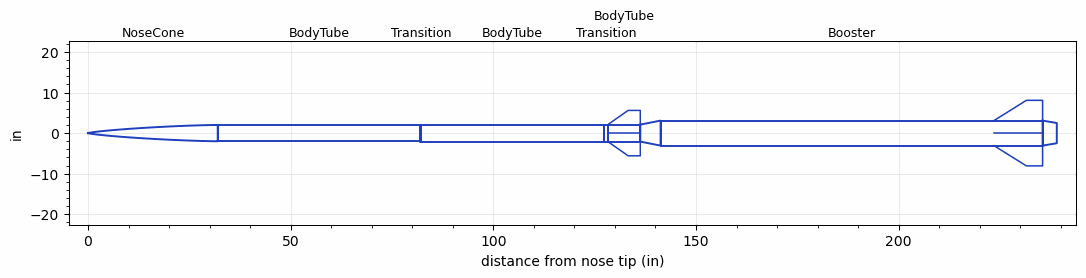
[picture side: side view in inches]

<RASAeroDocument>
 <FileVersion>2</FileVersion>
 <RocketDesign>
  <NoseCone>
   <Length>32</Length>
   <Diameter>4.02</Diameter>
   <Shape>Von Karman Ogive</Shape>
   <Location>0</Location>
  </NoseCone>
  <BodyTube>
   <Length>50</Length>
   <Diameter>4.02</Diameter>
   <Location>32</Location>
   <Protuberance>
    <StreamlinedNoBaseDrag>0.3693967</StreamlinedNoBaseDrag>
    <StreamlinedWithBaseDrag>0</StreamlinedWithBaseDrag>
    <InclinedPlate1Angle>0</InclinedPlate1Angle>
    <InclinedPlate1FrontalArea>0</InclinedPlate1FrontalArea>
    <InclinedPlate2Angle>0</InclinedPlate2Angle>
    <InclinedPlate2FrontalArea>0</InclinedPlate2FrontalArea>
   </Protuberance>
  </BodyTube>
  <Transition>
   <Length>0.25</Length>
   <Diameter>4.17</Diameter>
   <Location>82</Location>
   <RearDiameter>4.17</RearDiameter>
  </Transition>
  <BodyTube>
   <Length>45</Length>
   <Diameter>4.17</Diameter>
   <Location>82.25</Location>
  </BodyTube>
  <Transition>
   <Length>1</Length>
   <Diameter>4.2</Diameter>
   <Location>127.25</Location>
   <RearDiameter>4.2</RearDiameter>
  </Transition>
  <BodyTube>
   <Length>8</Length>
   <Diameter>4.2</Diameter>
   <Location>128.25</Location>
   <Fin>
    <Count>4</Count>
    <Chord>8</Chord>
    <Span>3.5</Span>
    <SweepDistance>5</SweepDistance>
    <TipChord>3</TipChord>
    <Thickness>0.25</Thickness>
    <Location>8</Location>
    <AirfoilSection>Hexagonal Blunt Base</AirfoilSection>
    <FX1>0.7469705</FX1>
   </Fin>
  </BodyTube>
  <Booster>
   <Length>94.25</Length>
   <Diameter>6.17</Diameter>
   <InsideDiameter>4.2</InsideDiameter>
   <Location>136.25</Location>
   <ShoulderLength>5</ShoulderLength>
   <BoattailLength>3.5</BoattailLength>
   <BoattailRearDiameter>5</BoattailRearDiameter>
   <Fin>
    <Count>4</Count>
    <Chord>12</Chord>
    <Span>5</Span>
    <SweepDistance>8</SweepDistance>
    <TipChord>4</TipChord>
    <Thickness>0.375</Thickness>
    <Location>12</Location>
    <AirfoilSection>Hexagonal Blunt Base</AirfoilSection>
    <FX1>1.120456</FX1>
   </Fin>
   <Protuberance>
    <StreamlinedNoBaseDrag>0.4531865</StreamlinedNoBaseDrag>
    <StreamlinedWithBaseDrag>0</StreamlinedWithBaseDrag>
    <InclinedPlate1Angle>0</InclinedPlate1Angle>
    <InclinedPlate1FrontalArea>0</InclinedPlate1FrontalArea>
    <InclinedPlate2Angle>0</InclinedPlate2Angle>
    <InclinedPlate2FrontalArea>0</InclinedPlate2FrontalArea>
   </Protuberance>
  </Booster>
  <Surface>Rough Camouflage Paint</Surface>
  <ModifiedBarrowman>False</ModifiedBarrowman>
  <Turbulence>False</Turbulence>
  <UseBooster1>True</UseBooster1>
  <UseBooster2>False</UseBooster2>
  <Comments>Iris Nov 8. Booster body simplified to constant 6.17 in over the cylindrical section; camera shells approximated as streamlined protuberances.</Comments>
 </RocketDesign>
 <LaunchSite>
  <Altitude>0</Altitude>
  <Pressure>29.9214</Pressure>
  <RodAngle>0</RodAngle>
  <RodLength>3.2808</RodLength>
  <Temperature>59</Temperature>
  <WindSpeed>4.4739</WindSpeed>
 </LaunchSite>
 <Recovery>
  <Altitude1>0</Altitude1>
  <Altitude2>0</Altitude2>
  <DeviceType1>None</DeviceType1>
  <DeviceType2>None</DeviceType2>
  <Event1>False</Event1>
  <Event2>False</Event2>
  <Size1>0</Size1>
  <Size2>0</Size2>
  <EventType1>None</EventType1>
  <EventType2>None</EventType2>
  <CD1>0</CD1>
  <CD2>0</CD2>
 </Recovery>
 <SimulationList>
  <Simulation>
   <SustainerEngine>N3366  (sustainer_2)</SustainerEngine>
   <SustainerLaunchWt>57.48783</SustainerLaunchWt>
   <SustainerCG>95.2372</SustainerCG>
   <SustainerIgnitionDelay>5</SustainerIgnitionDelay>
   <Booster1Engine>O6836  (iris-booster-13)</Booster1Engine>
   <Booster1LaunchWt>161.4426</Booster1LaunchWt>
   <Booster1SeparationDelay>5</Booster1SeparationDelay>
   <Booster1IgnitionDelay>0</Booster1IgnitionDelay>
   <Booster1CG>162.8691</Booster1CG>
   <IncludeBooster1>True</IncludeBooster1>
   <Booster2Delay>0</Booster2Delay>
   <IncludeBooster2>False</IncludeBooster2>
   <TimetoApogee>76.39581</TimetoApogee>
   <MaxAltitude>82555.71</MaxAltitude>
   <MaxVelocity>2849.808</MaxVelocity>
  </Simulation>
 </SimulationList>
</RASAeroDocument>
